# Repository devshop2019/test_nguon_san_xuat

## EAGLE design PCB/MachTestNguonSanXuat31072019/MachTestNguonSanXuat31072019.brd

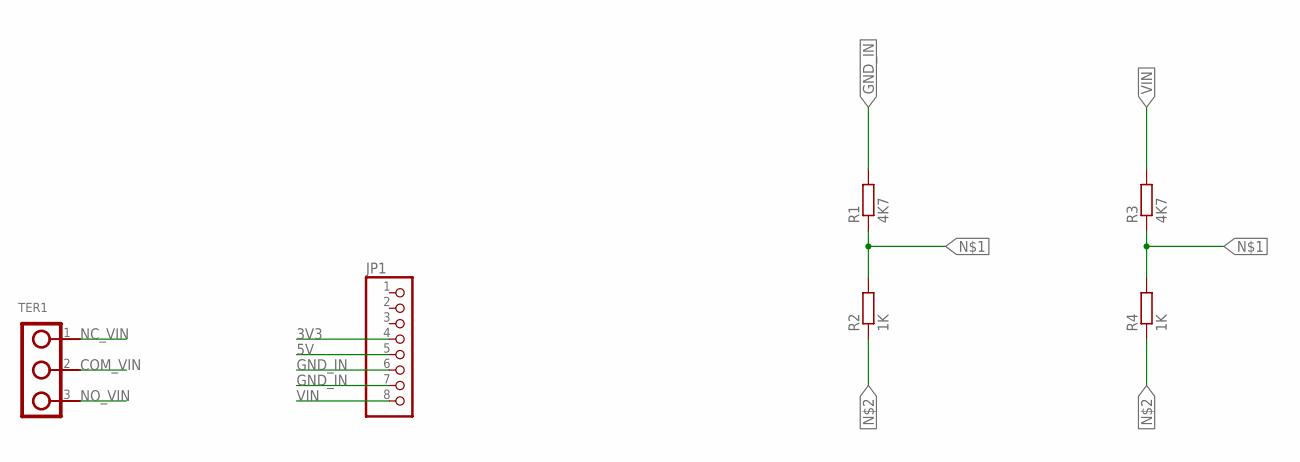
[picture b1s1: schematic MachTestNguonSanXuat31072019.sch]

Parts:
JP1: PINHD-1X8CLEANBIG; 1X08-CLEANBIG
R1, R3: 4K7; RCL_R0603
R2, R4: 1K; RCL_R0603
TER1: DOMINO-3

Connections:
3V3: JP1.4
5V: JP1.5
COM_VIN: TER1.2
GND_IN: JP1.6, JP1.7, R1.2
unnamed: R1.1, R2.2, R3.1, R4.2
unnamed: R2.1, R4.1
NC_VIN: TER1.1
NO_VIN: TER1.3
VIN: JP1.8, R3.2

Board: 2 copper layers, 6 parts (0 on the bottom side), 4 nets, no tracks yet.

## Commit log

2019-07-31 PCB, ino
2020-12-26 Add file tes gpio for Raspberry Pi 4
2020-12-26 Full test SPIO For Raspberry OK
2020-12-26 Update file Test GPIO raspberry
2021-10-12 Add arduino_board: Tool upload Super Fast
2021-10-13 Fix Input Com Manual for Nano Promini
